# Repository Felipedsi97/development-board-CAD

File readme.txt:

Both projects were made using Kicad 6.0

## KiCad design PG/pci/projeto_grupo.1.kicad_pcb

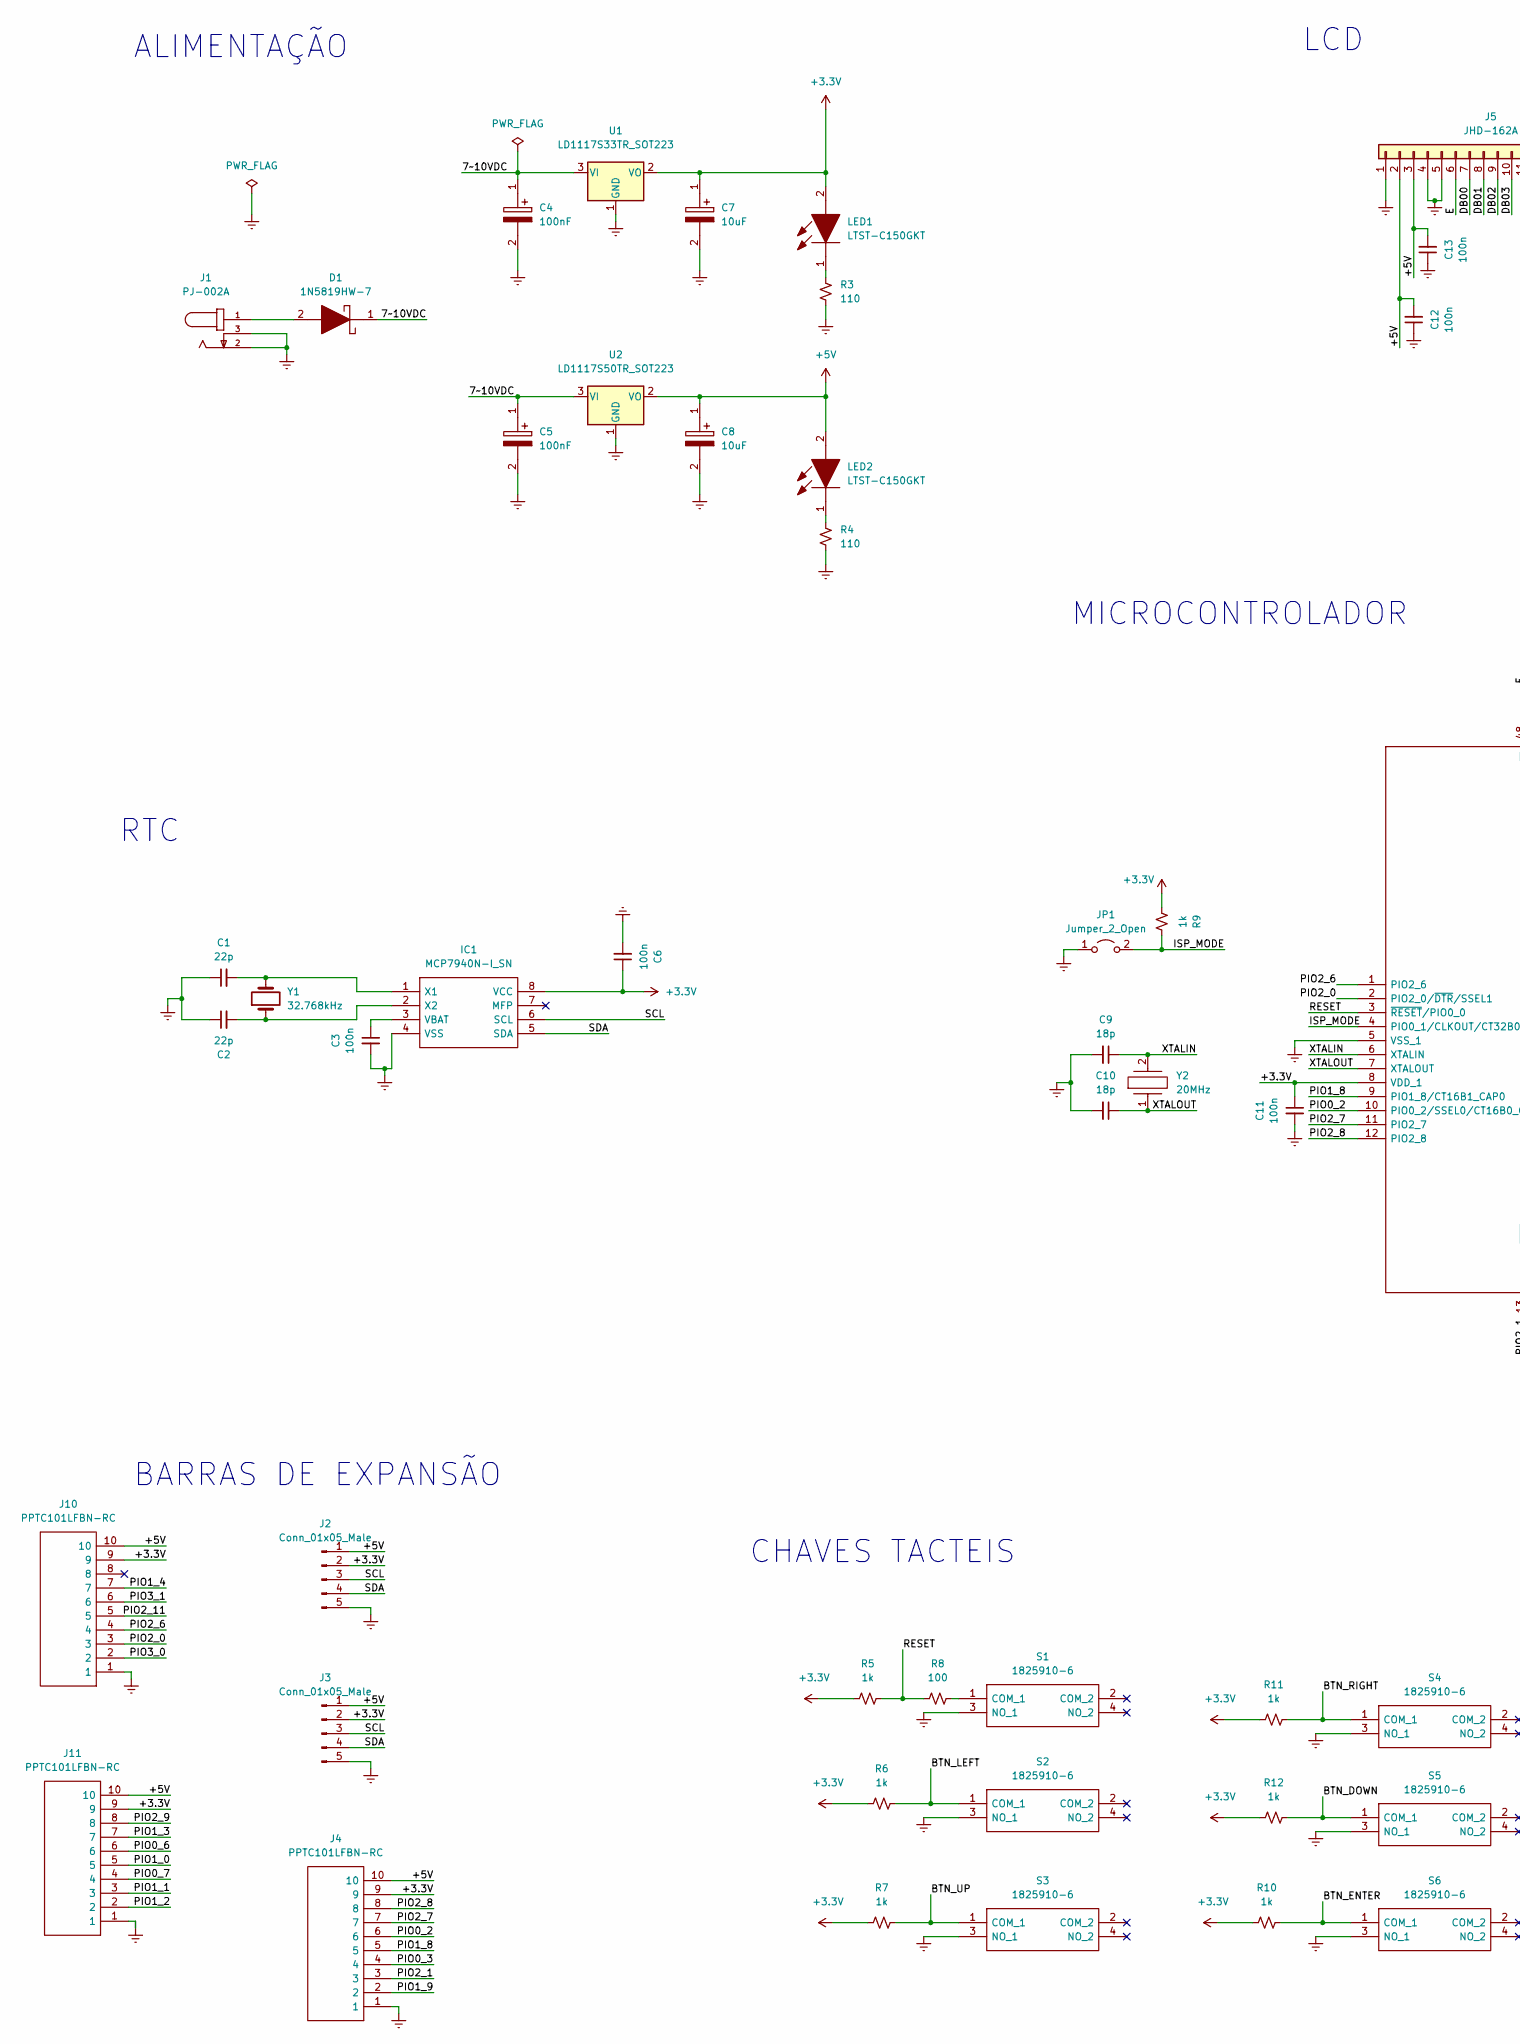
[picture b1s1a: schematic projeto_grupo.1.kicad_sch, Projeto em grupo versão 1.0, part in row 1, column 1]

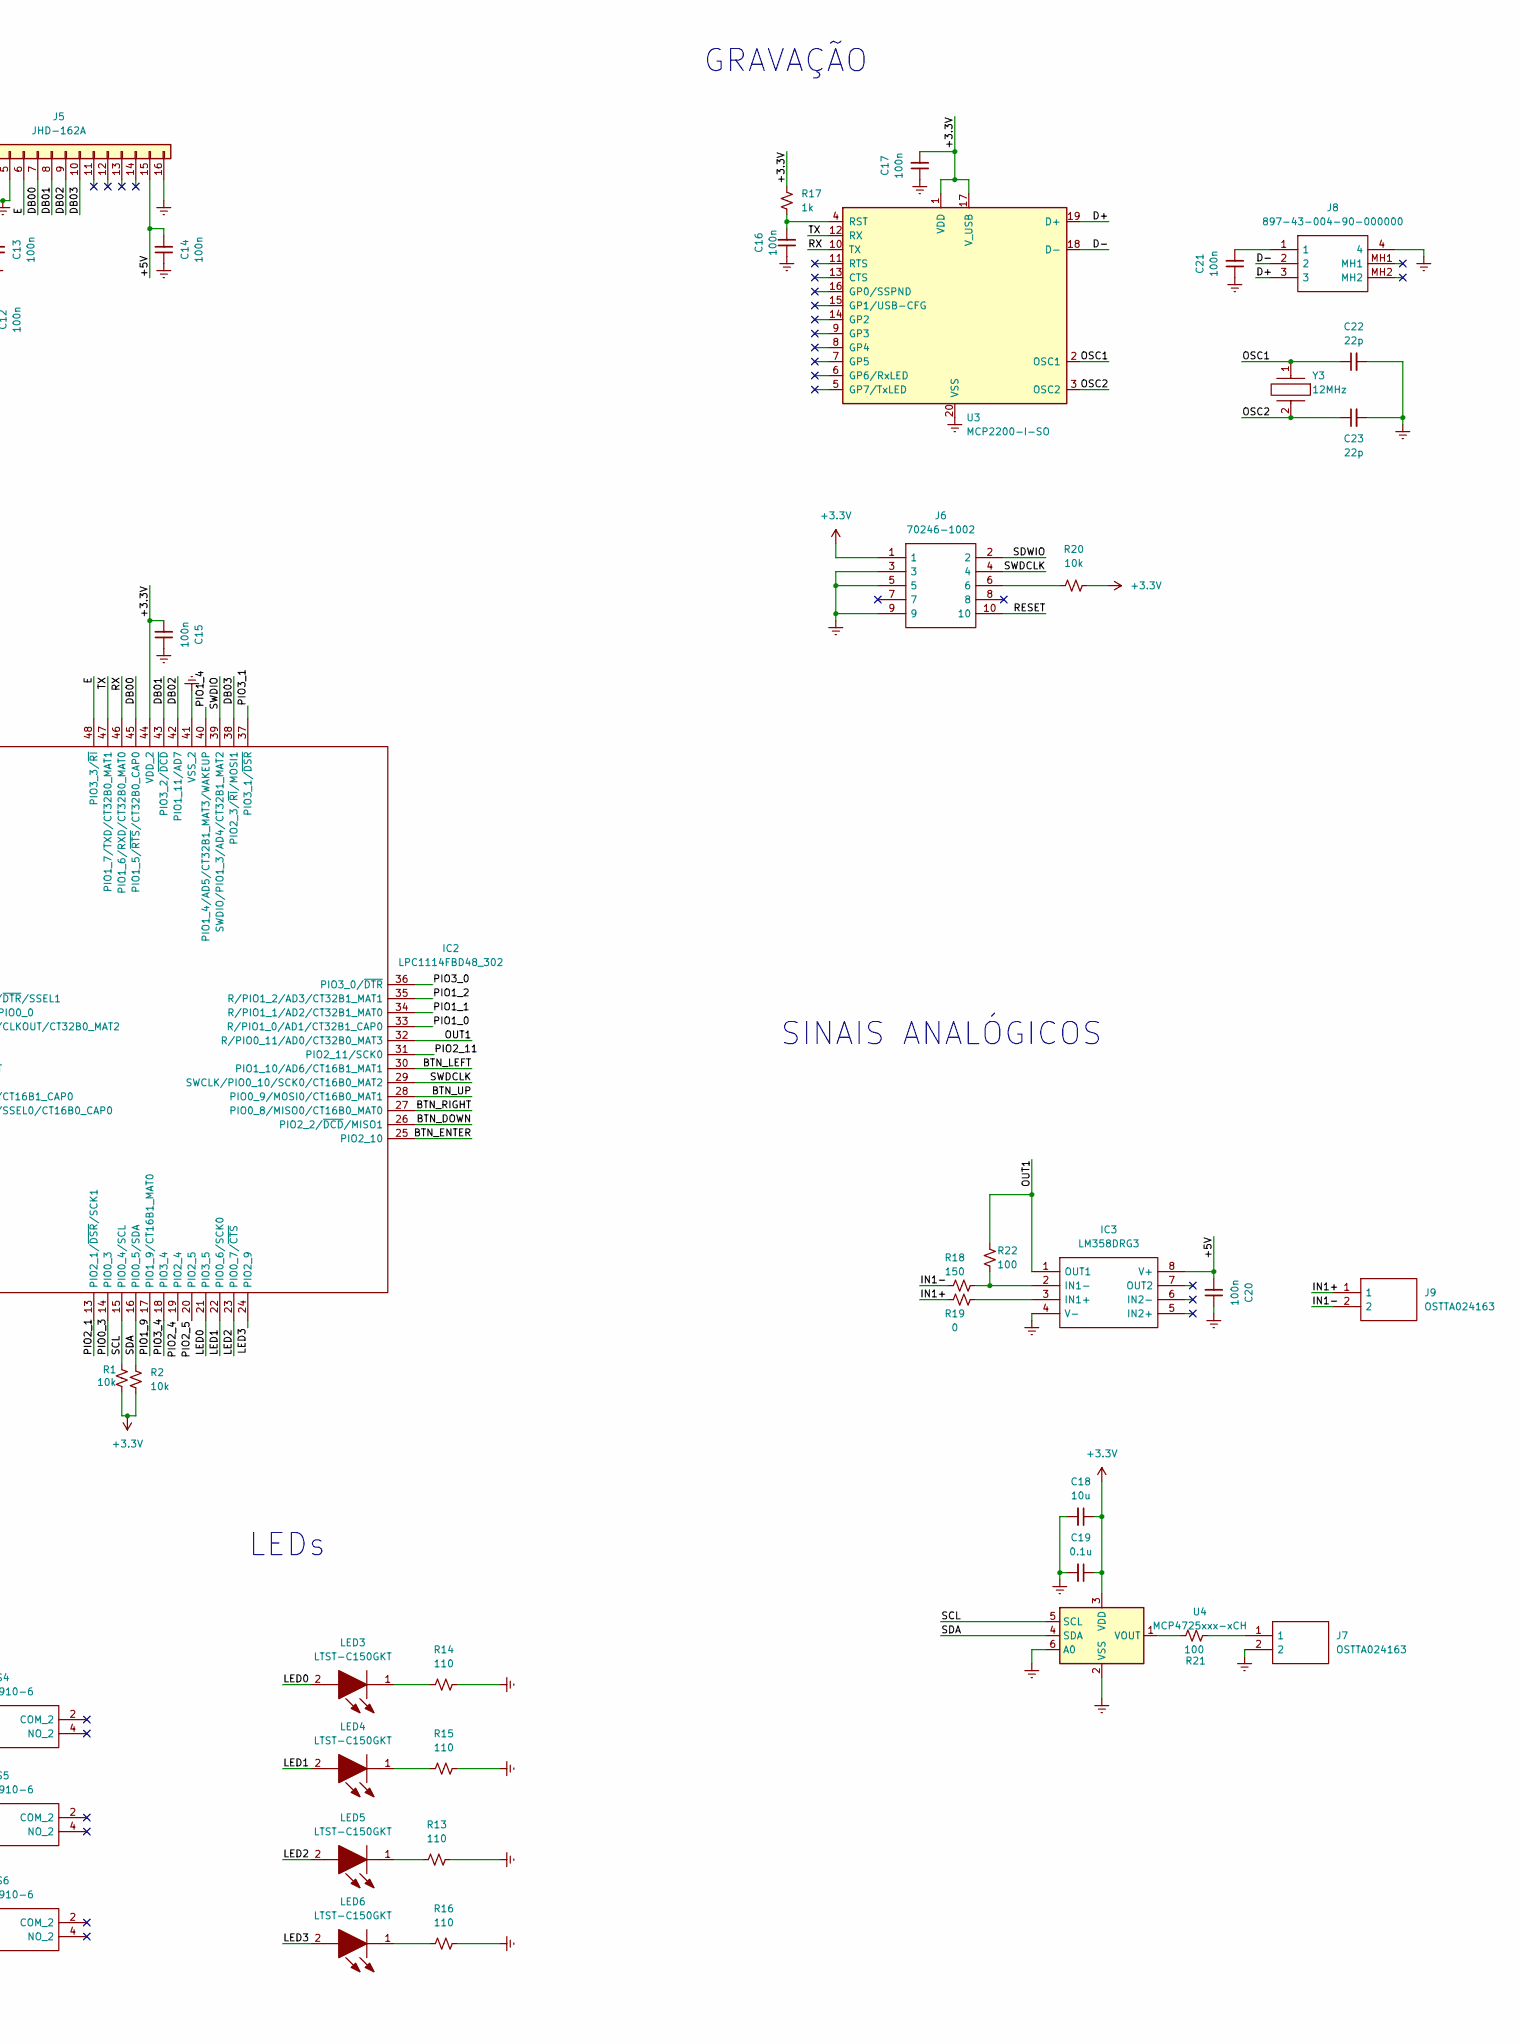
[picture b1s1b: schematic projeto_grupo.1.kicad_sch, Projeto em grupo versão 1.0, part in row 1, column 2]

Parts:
C1, C2, C22, C23: 22p; C_0805_2012Metric
C3, C6, C11, C12, C13, C14, C15, C16, C17, C20, C21: 100n; C_0805_2012Metric
C4, C5: 100nF; CAPAE330X550N; Mouser Part Number 710-865090368008
C7, C8: 10uF; CAPAE330X550N; Mouser Part Number 710-865090368008
C9, C10: 18p; C_0805_2012Metric
C18: 10u; C_0805_2012Metric
C19: 0.1u; C_0805_2012Metric
D1: 1N5819HW-7; SOD3716X135N; Manufacturer_Part_Number 1N5819HW-7; Mouser Part Number 621-1N5819HW
IC1: MCP7940N-I_SN; SOIC127P600X175-8N; Manufacturer_Part_Number MCP7940N-I/SN; Mouser Part Number 579-MCP7940N-I/SN
IC2: LPC1114FBD48_302; QFP50P900X900X160-48N; Manufacturer_Part_Number LPC1114FBD48/302; Mouser Part Number N/A
IC3: LM358DRG3; SOIC127P600X175-8N; Manufacturer_Part_Number LM358DRG3; Mouser Part Number 595-LM358DRG3
J1: PJ-002A; CUI_PJ-002A
J2, J3: Conn_01x05_Male; PinHeader_1x05_P2.54mm_Horizontal
J4, J10, J11: PPTC101LFBN-RC; RHDR10W80P0X254_1X10_2590X254X850P; Manufacturer_Part_Number PPTC101LFBN-RC
J5: JHD-162A; PinHeader_1x16_P2.54mm_Vertical
J6: 70246-1002; SHDR10W99P254_2X5_2032X889X947P; Manufacturer_Part_Number 70246-1002; Mouser Part Number 538-70246-1002
J7, J9: OSTTA024163; Manufacturer_Part_Number OSTTA024163
J8: 897-43-004-90-000000; 8974300490000000; Manufacturer_Part_Number 897-43-004-90-000000; Mouser Part Number 575-8974349
JP1: Jumper_2_Open; PinHeader_1x02_P2.54mm_Vertical
LED1, LED2, LED3, LED4, LED5, LED6: LTST-C150GKT; LEDC3216X120N; Manufacturer_Part_Number LTST-C150GKT; Mouser Part Number 859-LTST-C150GKT
R1, R2, R20: 10k; R_0805_2012Metric
R3, R4, R13, R14, R15, R16: 110; R_0805_2012Metric
R5, R6, R7, R9, R10, R11, R12, R17: 1k; R_0805_2012Metric
R8, R21, R22: 100; R_0805_2012Metric
R18: 150; R_0805_2012Metric
R19: 0; R_0805_2012Metric
S1, S2, S3, S4, S5, S6: 1825910-6; 18259106; Manufacturer_Part_Number 1825910-6; Mouser Part Number N/A
U1: LD1117S33TR_SOT223; SOT223
U2: LD1117S50TR_SOT223; SOT230P700X180-4N
U3: MCP2200-I-SO; SOIC127P1030X265-20N
U4: MCP4725xxx-xCH; SOT95P270X145-6N
Y1: 32.768kHz; AB38T32768KHZ
Y2: 20MHz; ATS20A; Manufacturer_Part_Number ATS12A; Mouser Part Number 774-ATS12A
Y3: 12MHz; ATS12A; Manufacturer_Part_Number ATS12A; Mouser Part Number 774-ATS12A

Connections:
+3.3V: C6.1, C7.1, C11.1, C15.2, C17.2, C18.1, C19.1, IC1.8 (VCC), IC2.8 (VDD_1), IC2.44 (VDD_2), J2.2, J3.2, J4.9, J6.1, J10.9, J11.9, LED1.2, R1.2, R2.2, R5.2, R6.2, R7.2, R9.2, R10.2, R11.2, R12.2, R17.1, R20.1, U1.2 (VO), U3.1 (VDD), U3.16 (GP0/SSPND), U3.17 (V_USB), U4.3 (VDD)
+5V: C8.1, C12.2, C13.2, C14.2, C20.2, IC3.8 (V+), J2.1, J3.1, J4.10, J5.2, J5.3, J5.15, J10.10, J11.10, LED2.2, U2.2 (VO)
/7~10VDC: C4.1, C5.1, D1.1, U1.3 (VI), U2.3 (VI)
/BTN_DOWN: IC2.26 (PIO2_2/~DCD/MISO1), R12.1, S5.1 (COM_1)
/BTN_ENTER: IC2.25 (PIO2_10), R10.1, S6.1 (COM_1)
/BTN_LEFT: IC2.30 (PIO1_10/AD6/CT16B1_MAT1), R6.1, S2.1 (COM_1)
/BTN_RIGHT: IC2.27 (PIO0_8/MISO0/CT16B0_MAT0), R11.1, S4.1 (COM_1)
/BTN_UP: IC2.28 (PIO0_9/MOSI0/CT16B0_MAT1), R7.1, S3.1 (COM_1)
/D+: J8.3, U3.19 (D+)
/D-: J8.2, U3.18 (D-)
/DB00: IC2.45 (PIO1_5/~RTS/CT32B0_CAP0), J5.7
/DB01: IC2.43 (PIO3_2/~DCD), J5.8
/DB02: IC2.42 (PIO1_11/AD7), J5.9
/DB03: IC2.38 (PIO2_3/~RI/MOSI1), J5.10
/E: IC2.48 (PIO3_3/~RI), J5.6
/IN1+: J9.1, R19.2
/IN1-: J9.2, R18.1
/ISP_MODE: IC2.4 (PIO0_1/CLKOUT/CT32B0_MAT2), JP1.2 (B), R9.1
/LED0: IC2.21 (PIO3_5), LED3.2
/LED1: IC2.22 (PIO0_6/SCK0), LED4.2
/LED2: IC2.23 (PIO0_7/~CTS), LED5.2
/LED3: IC2.24 (PIO2_9), LED6.2
/OSC1: C22.1, U3.2 (OSC1), Y3.1
/OSC2: C23.1, U3.3 (OSC2), Y3.2
/OUT1: IC2.32 (R/PIO0_11/AD0/CT32B0_MAT3), IC3.1 (OUT1), R22.1
/PIO0_2: IC2.10 (PIO0_2/SSEL0/CT16B0_CAP0), J4.6
/PIO0_3: IC2.14 (PIO0_3), J4.4
/PIO0_6: J11.6
/PIO0_7: J11.4
/PIO1_0: IC2.33 (R/PIO1_0/AD1/CT32B1_CAP0), J11.5
/PIO1_1: IC2.34 (R/PIO1_1/AD2/CT32B1_MAT0), J11.3
/PIO1_2: IC2.35 (R/PIO1_2/AD3/CT32B1_MAT1), J11.2
/PIO1_3: J11.7
/PIO1_4: IC2.40 (PIO1_4/AD5/CT32B1_MAT3/WAKEUP), J10.7
/PIO1_8: IC2.9 (PIO1_8/CT16B1_CAP0), J4.5
/PIO1_9: IC2.17 (PIO1_9/CT16B1_MAT0), J4.2
/PIO2_0: IC2.2 (PIO2_0/~DTR/SSEL1), J10.3
/PIO2_1: IC2.13 (PIO2_1/~DSR/SCK1), J4.3
/PIO2_4: IC2.19 (PIO2_4)
/PIO2_5: IC2.20 (PIO2_5)
/PIO2_6: IC2.1 (PIO2_6), J10.4
/PIO2_7: IC2.11 (PIO2_7), J4.7
/PIO2_8: IC2.12 (PIO2_8), J4.8
/PIO2_9: J11.8
/PIO2_11: IC2.31 (PIO2_11/SCK0), J10.5
/PIO3_0: IC2.36 (PIO3_0/~DTR), J10.2
/PIO3_1: IC2.37 (PIO3_1/~DSR), J10.6
/PIO3_4: IC2.18 (PIO3_4)
/RESET: IC2.3 (~RESET/PIO0_0), J6.10, R5.1, R8.2
/RX: IC2.46 (PIO1_6/RXD/CT32B0_MAT0), U3.10 (TX)
/SCL: IC1.6 (SCL), IC2.15 (PIO0_4/SCL), J2.3, J3.3, R1.1, U4.5 (SCL)
/SDA: IC1.5 (SDA), IC2.16 (PIO0_5/SDA), J2.4, J3.4, R2.1, U4.4 (SDA)
/SDWIO: J6.2
/SWDCLK: IC2.29 (SWCLK/PIO0_10/SCK0/CT16B0_MAT2), J6.4
/SWDIO: IC2.39 (SWDIO/PIO1_3/AD4/CT32B1_MAT2)
/TX: IC2.47 (PIO1_7/TXD/CT32B0_MAT1), U3.12 (RX)
/XTALIN: C9.1, IC2.6 (XTALIN), Y2.2
/XTALOUT: C10.1, IC2.7 (XTALOUT), Y2.1
Earth: C1.1, C2.1, C3.2, C4.2, C5.2, C6.2, C7.2, C8.2, C9.2, C10.2, C11.2, C12.1, C13.1, C14.1, C15.1, C16.1, C17.1, C18.2, C19.2, C20.1, C21.1, C22.2, C23.2, IC1.4 (VSS), IC2.5 (VSS_1), IC2.41 (VSS_2), IC3.4 (V-), J1.2, J1.3, J2.5, J3.5, J4.1, J5.1, J5.4, J5.5, J5.16, J6.3, J6.5, J6.9, J7.2, J8.4, J10.1, J11.1, JP1.1 (A), R3.2, R4.2, R13.1, R14.1, R15.1, R16.1, S1.3 (NO_1), S2.3 (NO_1), S3.3 (NO_1), S4.3 (NO_1), S5.3 (NO_1), S6.3 (NO_1), U1.1 (GND), U2.1 (GND), U3.20 (VSS), U4.2 (VSS), U4.6 (A0)
unnamed: C1.2, IC1.1 (X1), Y1.2
unnamed: C2.2, IC1.2 (X2), Y1.1
unnamed: C3.1, IC1.3 (VBAT)
unnamed: C16.2, R17.2, U3.4 (RST)
unnamed: C21.2, J8.1
unnamed: D1.2, J1.1
unnamed: IC3.2 (IN1-), R18.2, R22.2
unnamed: IC3.3 (IN1+), R19.1
unnamed: J6.6, R20.2
unnamed: J7.1, R21.1
unnamed: LED1.1, R3.1
unnamed: LED2.1, R4.1
unnamed: LED3.1, R14.2
unnamed: LED4.1, R15.2
unnamed: LED5.1, R13.2
unnamed: LED6.1, R16.2
unnamed: R8.1, S1.1 (COM_1)
unnamed: R21.2, U4.1 (VOUT)

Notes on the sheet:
SINAIS ANALÓGICOS
LEDs
GRAVAÇÃO
CHAVES TACTEIS
MICROCONTROLADOR
RTC
ALIMENTAÇÃO
LCD
BARRAS DE EXPANSÃO

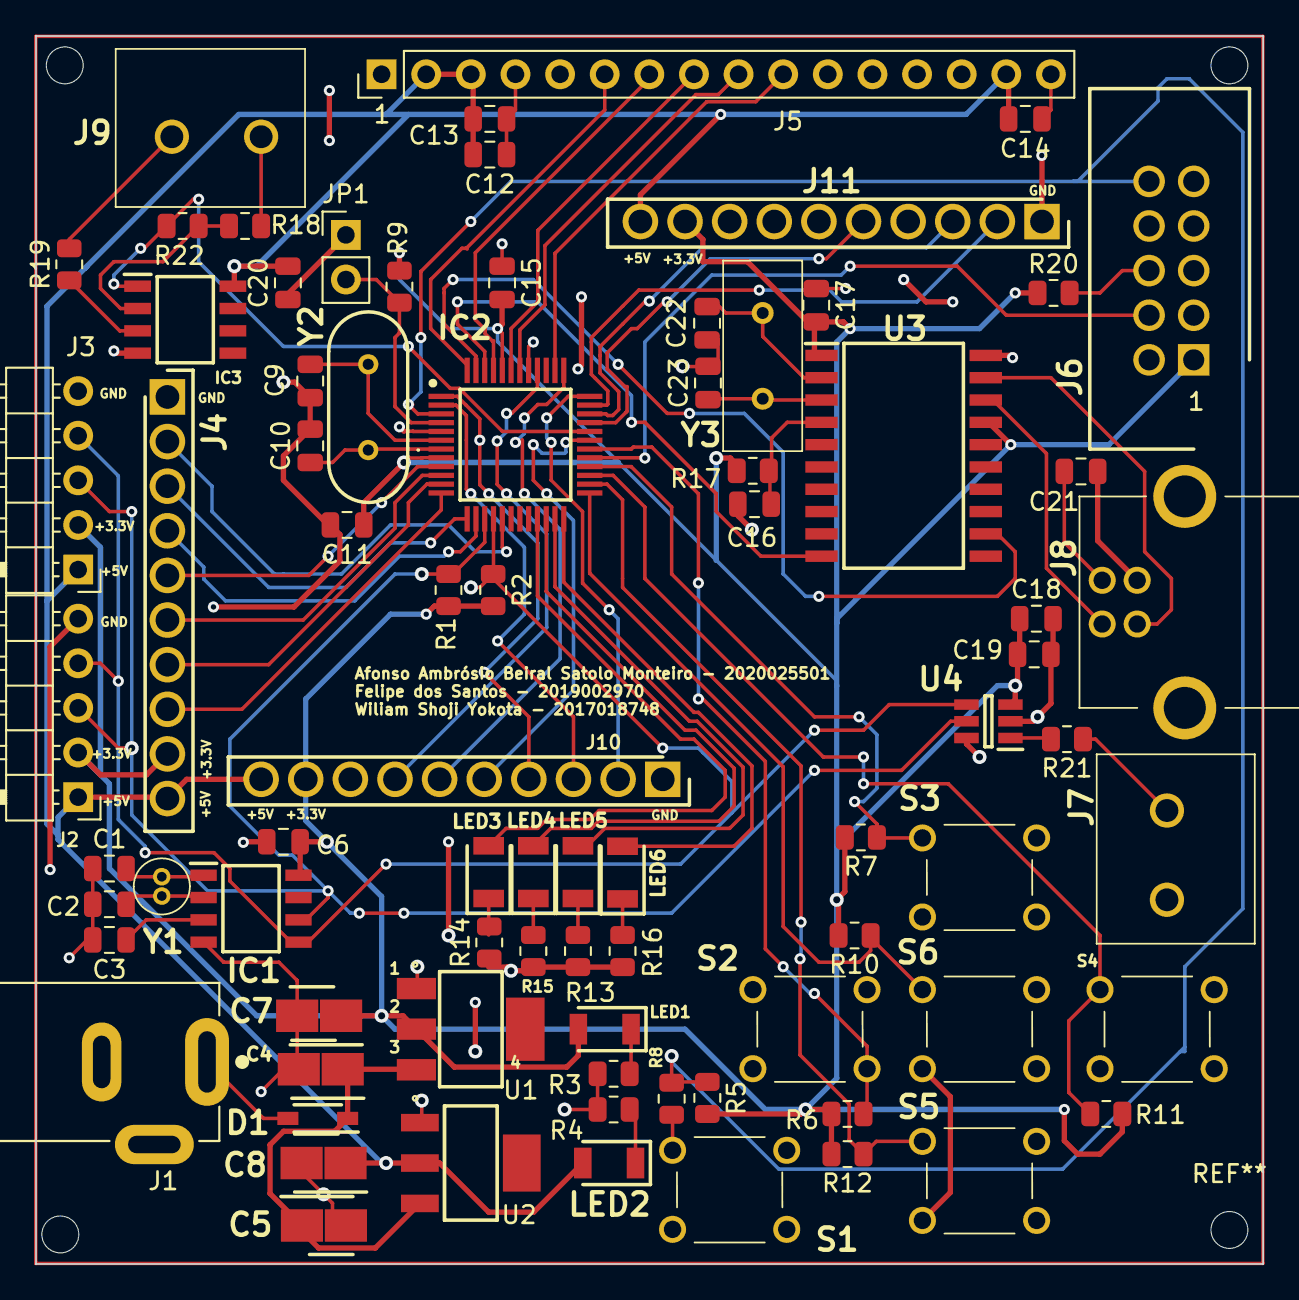
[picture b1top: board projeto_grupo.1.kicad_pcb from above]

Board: 2 copper layers, 69.9 x 69.9 mm, 80 parts (0 on the bottom side), 68 nets.

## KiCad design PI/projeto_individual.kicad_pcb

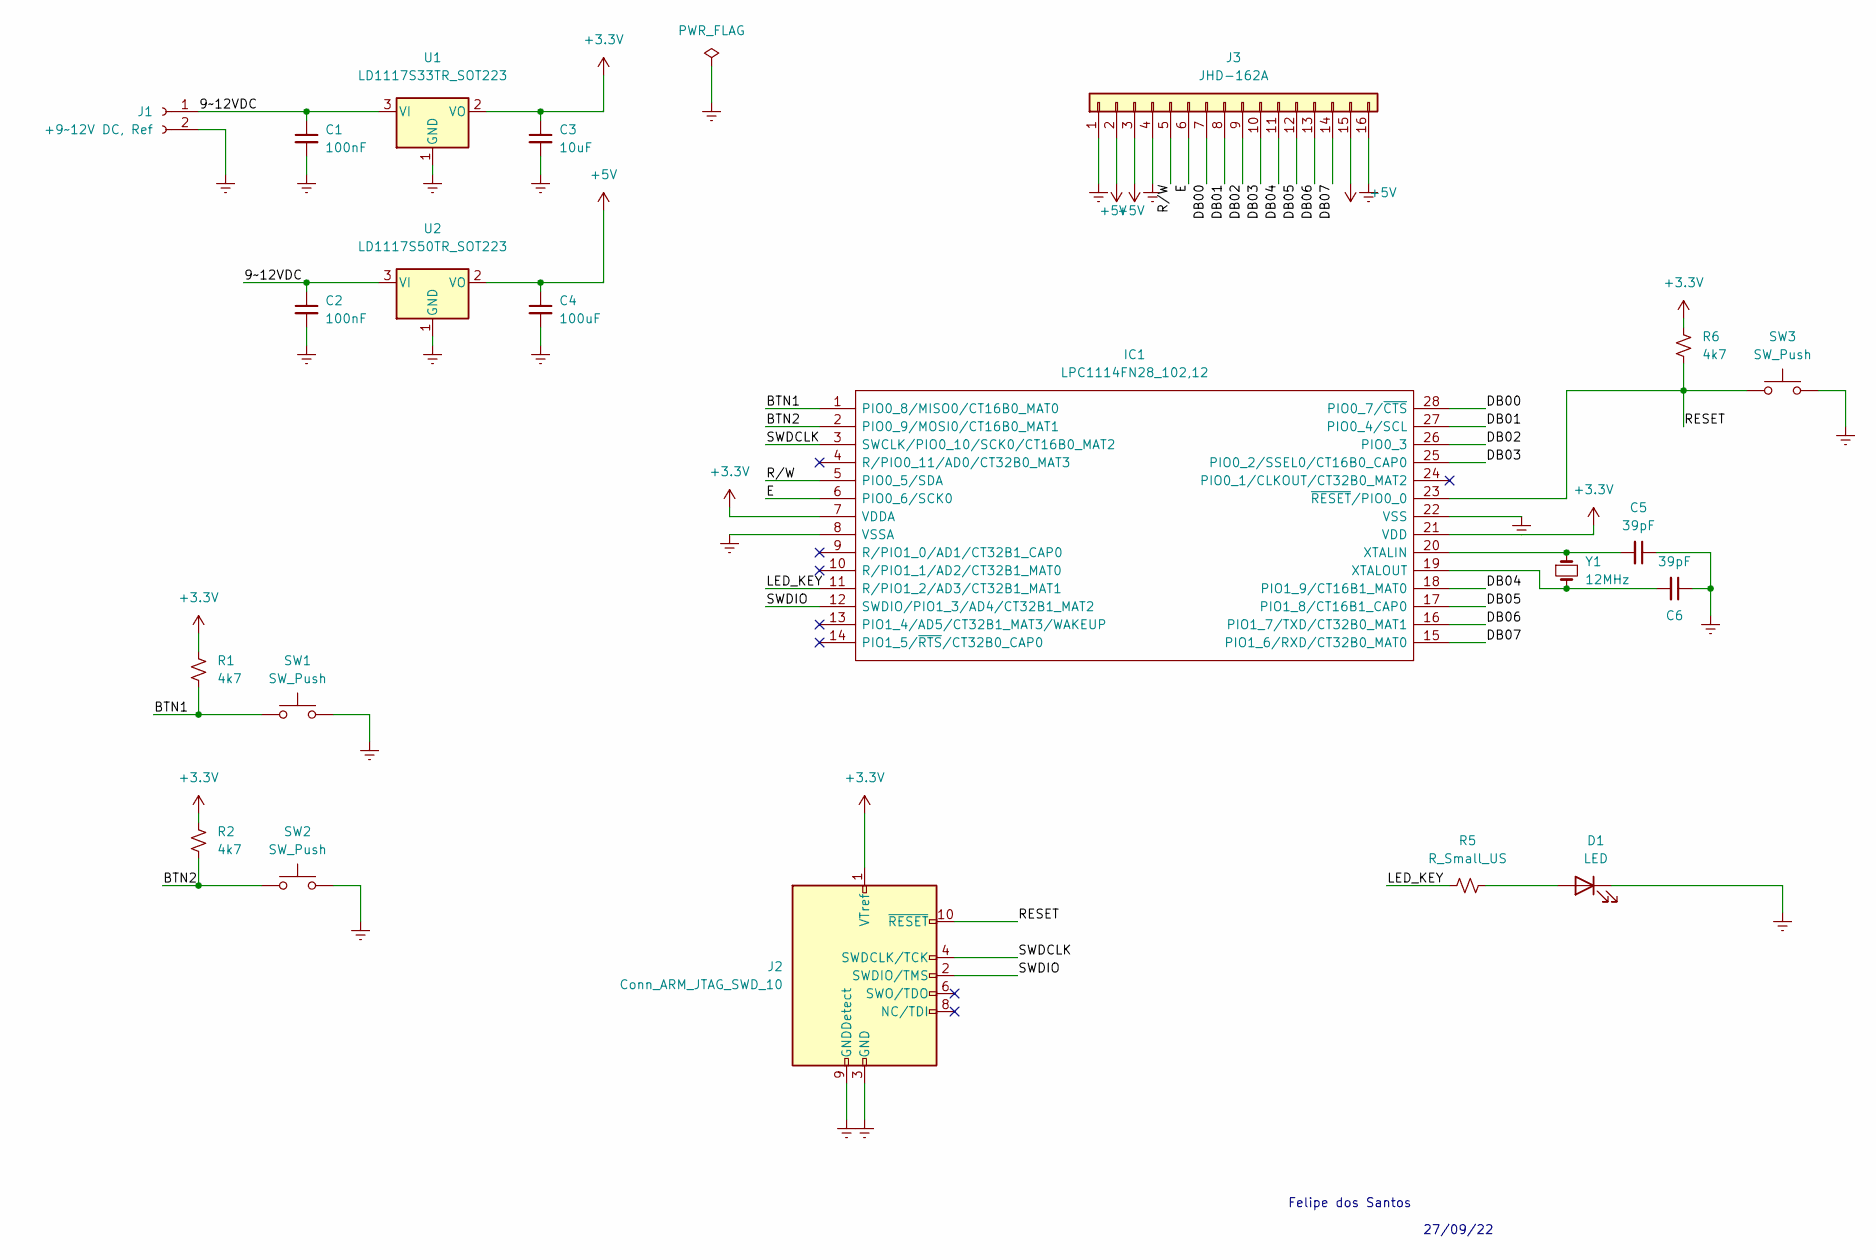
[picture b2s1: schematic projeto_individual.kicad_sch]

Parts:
C1, C2: 100nF; C_0805_2012Metric
C3: 10uF; C_0805_2012Metric
C4: 100uF; C_0805_2012Metric
C5, C6: 39pF; C_0805_2012Metric
D1: LED; LEDC3216X120N
IC1: LPC1114FN28_102,12; DIP1552W53P254L3550H510Q28N; Manufacturer_Part_Number LPC1114FN28/102,12; Mouser Part Number 771-LPC1114FN28/1021
J1: +9~12V DC, Ref; CUI_PJ-002A
J2: Conn_ARM_JTAG_SWD_10; PinHeader_2x05_P2.54mm_Horizontal
J3: JHD-162A; PinHeader_1x16_P1.00mm_Horizontal
R1, R2, R6: 4k7; R_0805_2012Metric
R5: R_Small_US; R_0805_2012Metric
SW1, SW2, SW3: SW_Push; 1825910-6
U1: LD1117S33TR_SOT223; SOT-223-3_TabPin2
U2: LD1117S50TR_SOT223; SOT-223-3_TabPin2
Y1: 12MHz; XTAL_HC49P488W43L1085T450H368

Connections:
+3.3V: C3.1, IC1.7 (VDDA), IC1.21 (VDD), J2.1 (VTref), R1.1, R2.1, R6.1, U1.2 (VO)
+5V: C4.1, J3.2, J3.3, J3.15, U2.2 (VO)
/BTN1: IC1.1 (PIO0_8/MISO0/CT16B0_MAT0), R1.2, SW1.1
/BTN2: IC1.2 (PIO0_9/MOSI0/CT16B0_MAT1), R2.2, SW2.1
/DB00: IC1.28 (PIO0_7/~CTS), J3.7
/DB01: IC1.27 (PIO0_4/SCL), J3.8
/DB02: IC1.26 (PIO0_3), J3.9
/DB03: IC1.25 (PIO0_2/SSEL0/CT16B0_CAP0), J3.10
/DB04: IC1.18 (PIO1_9/CT16B1_MAT0), J3.11
/DB05: IC1.17 (PIO1_8/CT16B1_CAP0), J3.12
/DB06: IC1.16 (PIO1_7/TXD/CT32B0_MAT1), J3.13
/DB07: IC1.15 (PIO1_6/RXD/CT32B0_MAT0), J3.14
/E: IC1.6 (PIO0_6/SCK0), J3.6
/LED_KEY: IC1.11 (R/PIO1_2/AD3/CT32B1_MAT1), R5.1
/RESET: IC1.23 (~RESET/PIO0_0), J2.10 (~RESET), R6.2, SW3.1
/R/W: IC1.5 (PIO0_5/SDA), J3.5
/SWDCLK: IC1.3 (SWCLK/PIO0_10/SCK0/CT16B0_MAT2), J2.4 (SWDCLK/TCK)
/SWDIO: IC1.12 (SWDIO/PIO1_3/AD4/CT32B1_MAT2), J2.2 (SWDIO/TMS)
Earth: C1.2, C2.2, C3.2, C4.2, C5.1, C6.1, D1.1 (K), IC1.8 (VSSA), IC1.22 (VSS), J1.2, J2.3 (GND), J2.5 (GND), J2.9 (GNDDetect), J3.1, J3.4, J3.16, SW1.2, SW2.2, SW3.2, U1.1 (GND), U2.1 (GND)
unnamed: C5.2, IC1.20 (XTALIN), Y1.1
unnamed: C6.2, IC1.19 (XTALOUT), Y1.2
unnamed: D1.2 (A), R5.2

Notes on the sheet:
27/09/22
Felipe dos Santos

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
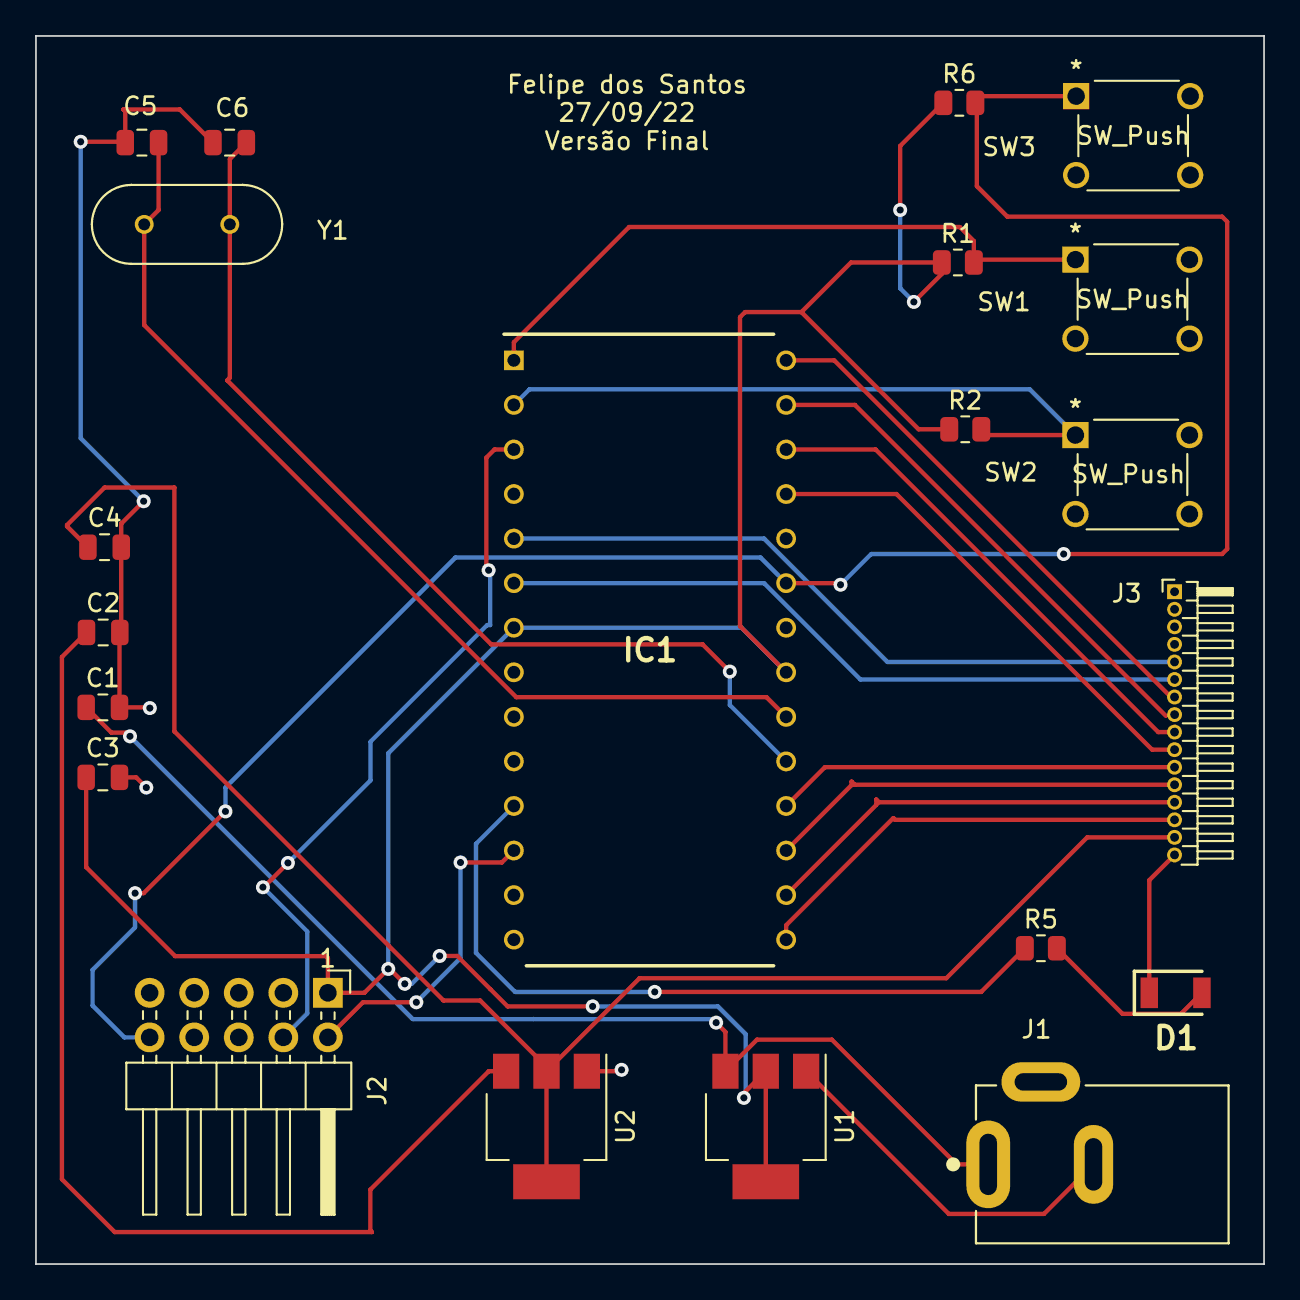
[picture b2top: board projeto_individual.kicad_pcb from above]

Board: 2 copper layers, 70.0 x 70.0 mm, 21 parts (0 on the bottom side), 24 nets.

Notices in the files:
parts and their libraries:
Copyright 2021 Accelerated Designs. All rights reserved.
